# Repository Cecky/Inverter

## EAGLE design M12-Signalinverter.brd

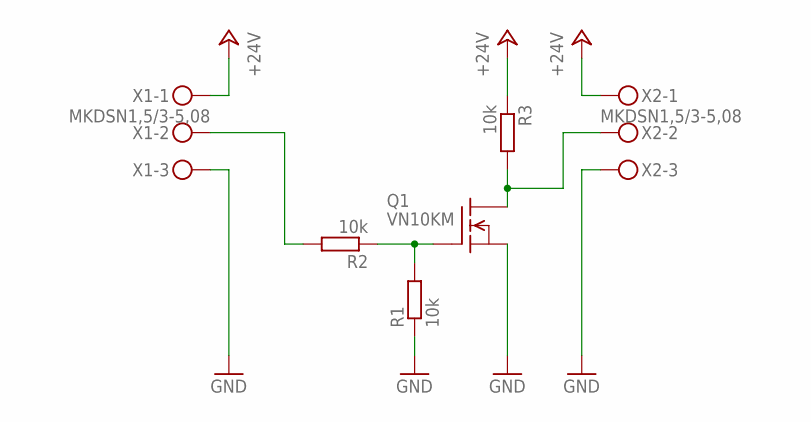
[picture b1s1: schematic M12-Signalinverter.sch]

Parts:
Q1: VN10KM; TO237
R1, R2, R3: 10k; 0207/7
X1, X2: MKDSN1,5/3-5,08

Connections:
+24V: R3.1, X1.1, X2.1
GND: Q1.3 (S), R1.1, X1.3, X2.3
unnamed: Q1.1 (D), R3.2, X2.2
unnamed: Q1.2 (G), R1.2, R2.1
unnamed: R2.2, X1.2

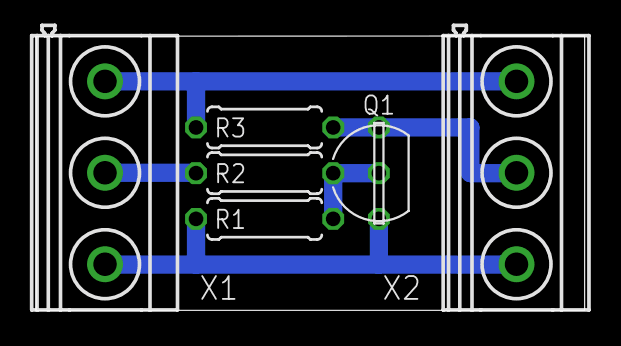
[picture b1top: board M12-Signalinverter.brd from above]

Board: 2 copper layers, 30.5 x 15.2 mm, 6 parts (0 on the bottom side), 5 nets.

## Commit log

2020-01-13 Init
